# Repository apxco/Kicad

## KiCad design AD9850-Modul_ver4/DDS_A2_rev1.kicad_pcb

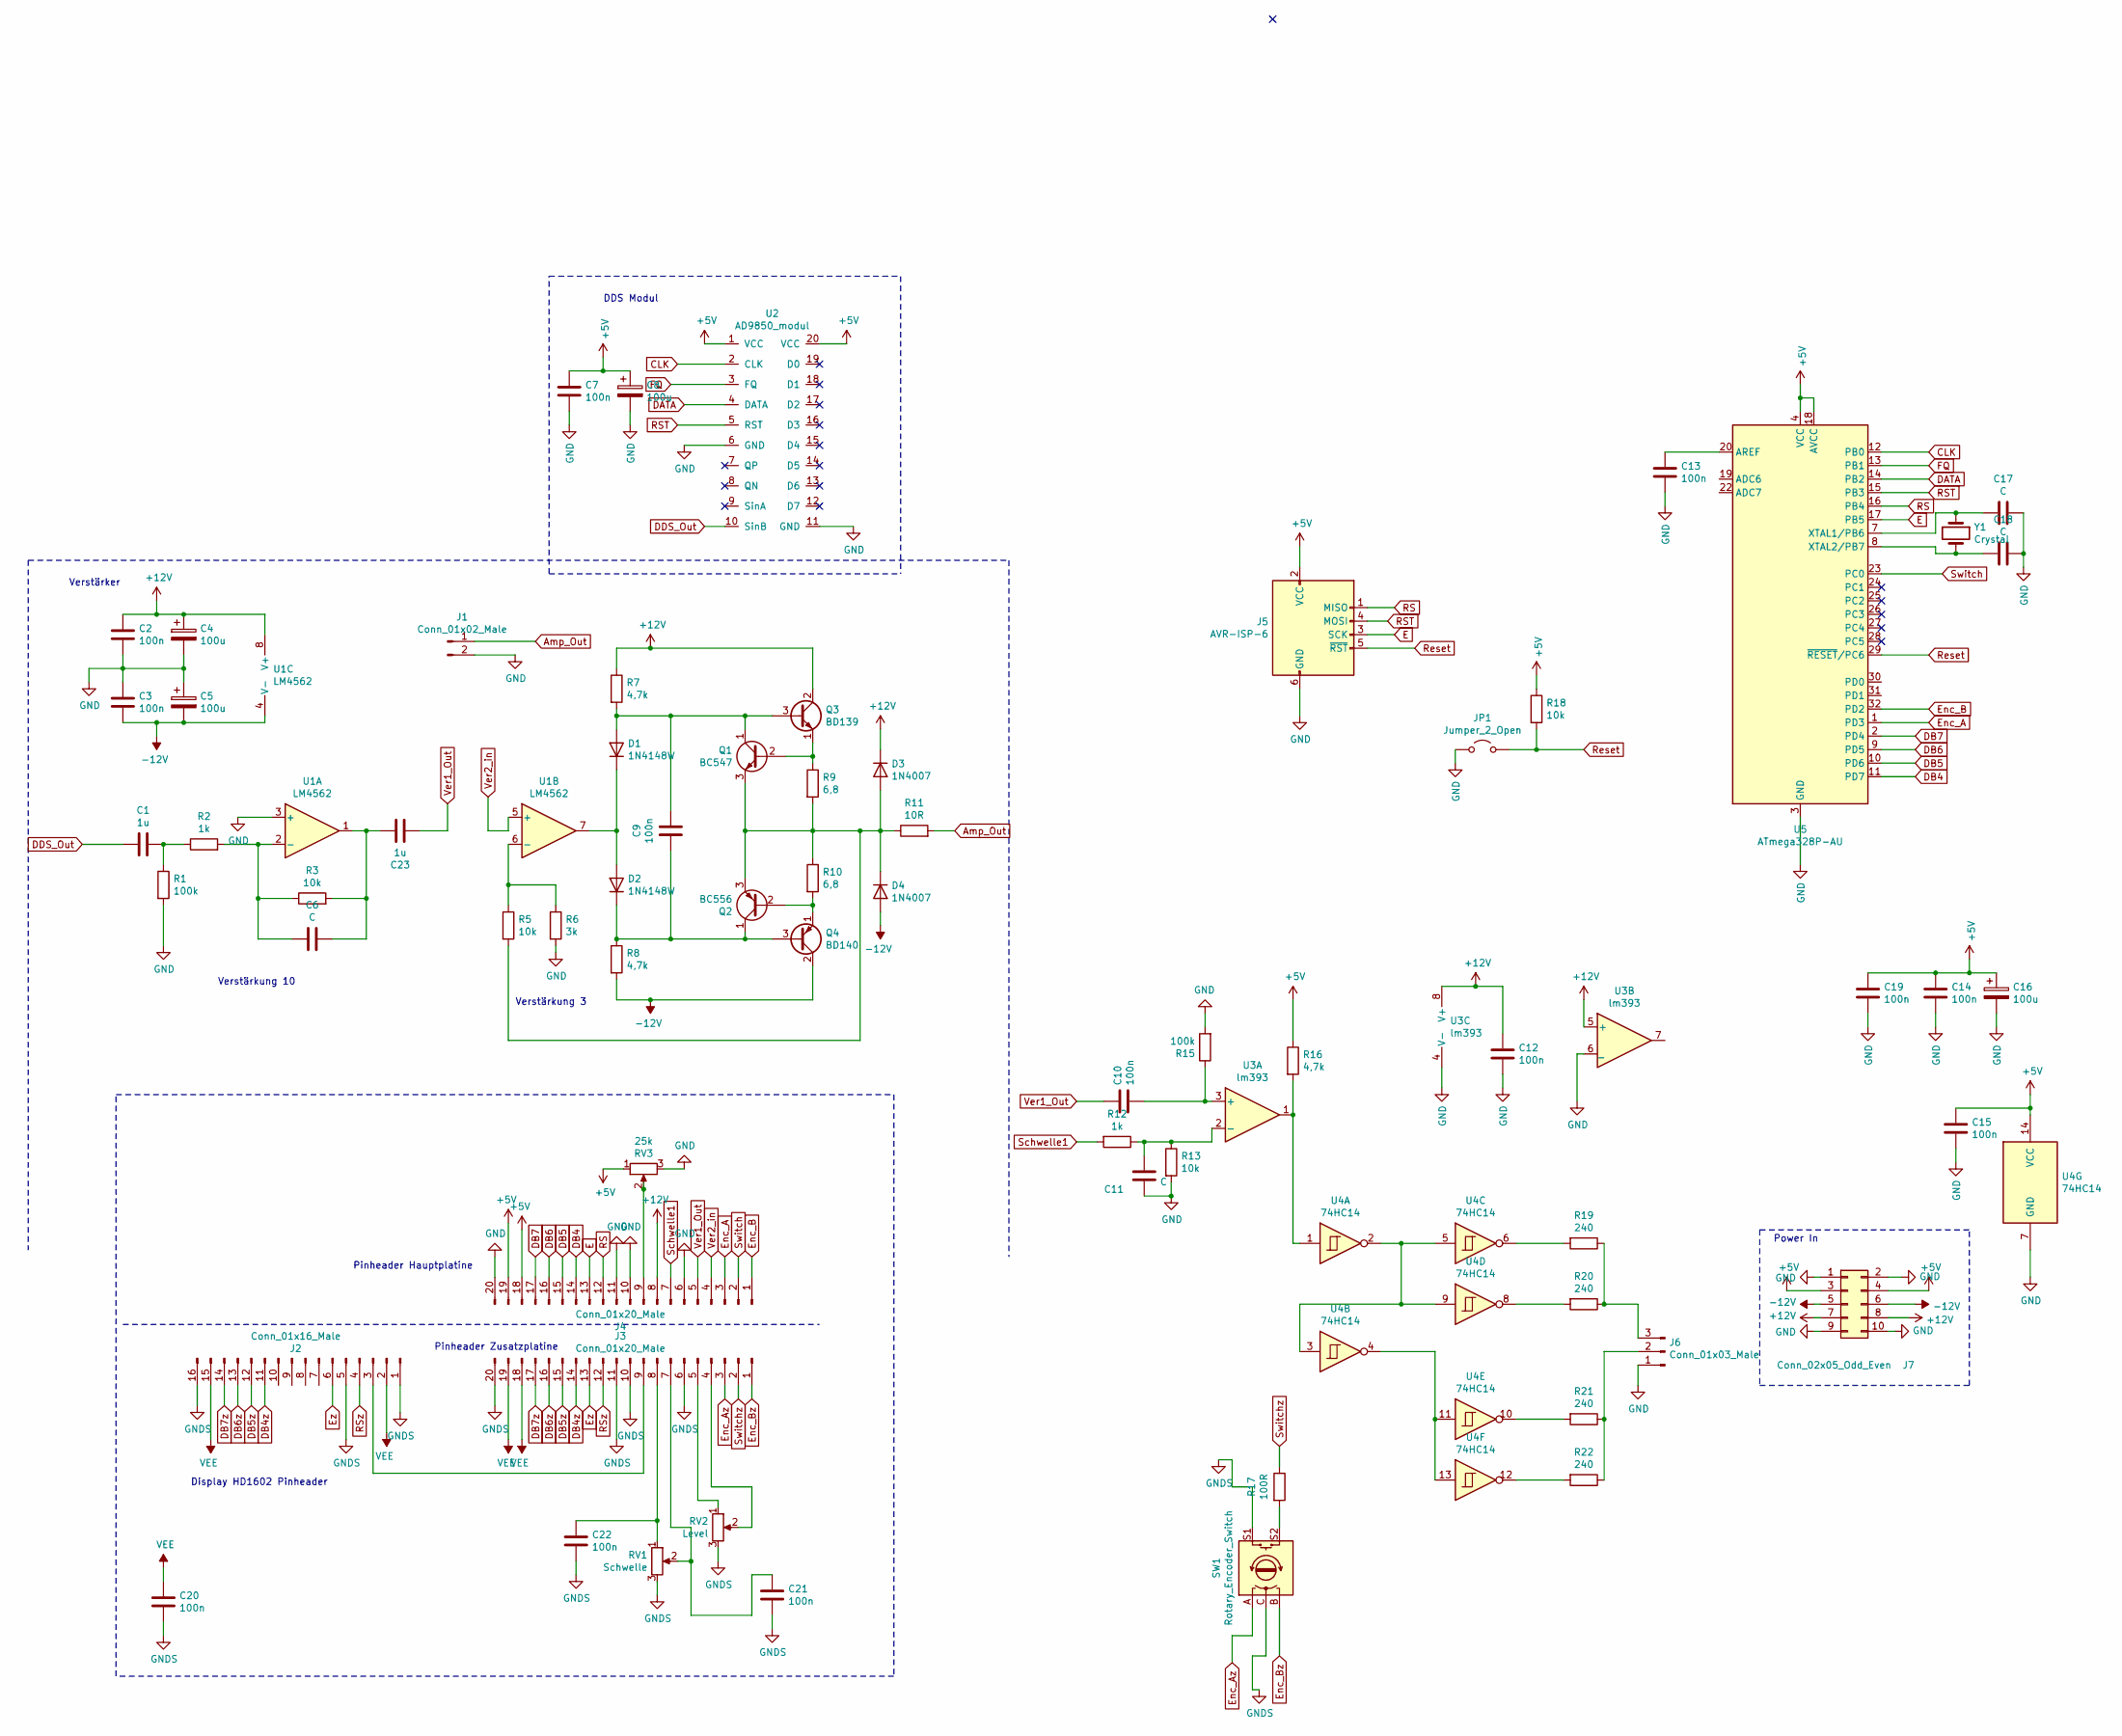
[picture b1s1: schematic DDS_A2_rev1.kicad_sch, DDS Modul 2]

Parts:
C1, C23: 1u; C_0805_2012Metric_Pad1.15x1.40mm_HandSolder
C2, C3, C7, C9, C10, C12, C13, C14, C15, C19, C20, C21, C22: 100n; C_0805_2012Metric_Pad1.15x1.40mm_HandSolder
C4, C5, C8, C16: 100u; CP_Radial_D5.0mm_P2.50mm
C6, C11: C; C_0805_2012Metric_Pad1.15x1.40mm_HandSolder
C17, C18: C; C_0603_1608Metric_Pad1.05x0.95mm_HandSolder
D1, D2: 1N4148W; D_SOD-123
D3, D4: 1N4007; D_DO-41_SOD81_P10.16mm_Horizontal
J1: Conn_01x02_Male; PinHeader_1x02_P2.54mm_Vertical
J2: Conn_01x16_Male; PinHeader_1x16_P2.54mm_Vertical
J3, J4: Conn_01x20_Male; PinHeader_1x20_P2.54mm_Vertical
J5: AVR-ISP-6; PinHeader_2x03_P2.54mm_Vertical
J6: Conn_01x03_Male; PinHeader_1x03_P2.54mm_Vertical
J7: Conn_02x05_Odd_Even; PinHeader_2x05_P2.54mm_Vertical
JP1: Jumper_2_Open; SolderJumper-2_P1.3mm_Bridged_Pad1.0x1.5mm
Q1: BC547; TO-92_Inline
Q2: BC556; TO-92_Inline
Q3: BD139; TO-126-3_Vertical
Q4: BD140; TO-126-3_Vertical
R1, R15: 100k; R_0805_2012Metric_Pad1.15x1.40mm_HandSolder
R2, R12: 1k; R_0805_2012Metric_Pad1.15x1.40mm_HandSolder
R3, R5, R13, R18: 10k; R_0805_2012Metric_Pad1.15x1.40mm_HandSolder
R6: 3k; R_0805_2012Metric_Pad1.15x1.40mm_HandSolder
R7, R8, R16: 4,7k; R_0805_2012Metric_Pad1.15x1.40mm_HandSolder
R9, R10: 6,8; R_2512_6332Metric_Pad1.52x3.35mm_HandSolder
R11: 10R; R_2512_6332Metric_Pad1.52x3.35mm_HandSolder
R17: 100R; R_0805_2012Metric_Pad1.15x1.40mm_HandSolder
R19, R20, R21, R22: 240; R_0805_2012Metric_Pad1.15x1.40mm_HandSolder
RV1: Schwelle; Potentiometer_Bourns_PTV09A-1_Single_Vertical
RV2: Level; Potentiometer_Bourns_PTV09A-1_Single_Vertical
RV3: 25k; Potentiometer_Bourns_3296W_Vertical
SW1: Rotary_Encoder_Switch; RotaryEncoder_Alps_EC11E-Switch_Vertical_H20mm
U1: LM4562; SOIC-8_3.9x4.9mm_P1.27mm
U2: AD9850_modul; AD9850modul
U3: lm393; SOIC-8_3.9x4.9mm_P1.27mm
U4: 74HC14; SOIC-14_3.9x8.7mm_P1.27mm
U5: ATmega328P-AU; TQFP-32_7x7mm_P0.8mm
Y1: Crystal; Crystal_HC18-U_Vertical

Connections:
+5V: C7.1, C8.1, C14.1, C15.1, C16.1, C19.1, J4.18, J4.19, J5.2 (VCC), J7.3, J7.4, R16.1, R18.1, RV3.1, U2.1 (VCC), U2.20 (VCC), U4.14 (VCC), U5.4 (VCC), U5.6 (VCC), U5.18 (AVCC)
+12V: C2.1, C4.1, C12.1, D3.1 (K), J4.8, J7.7, J7.8, Q3.2 (C), R7.1, U1.8 (V+), U3.5 (+), U3.8 (V+)
-12V: C3.2, C5.2, D4.2 (A), J7.5, J7.6, Q4.2 (C), R8.2, U1.4 (V-)
Amp_Out: J1.1, R11.2
CLK: U2.2 (CLK), U5.12 (PB0)
DATA: U2.4 (DATA), U5.14 (PB2)
DB4: J4.14, U5.11 (PD7)
DB4z: J2.11, J3.14
DB5: J4.15, U5.10 (PD6)
DB5z: J2.12, J3.15
DB6: J4.16, U5.9 (PD5)
DB6z: J2.13, J3.16
DB7: J4.17, U5.2 (PD4)
DB7z: J2.14, J3.17
DDS_Out: C1.2, U2.10 (SinB)
E: J4.13, J5.3 (SCK), U5.17 (PB5)
Enc_A: J4.3, U5.1 (PD3)
Enc_Az: J3.3, SW1.A
Enc_B: J4.1, U5.32 (PD2)
Enc_Bz: J3.1, SW1.B
Ez: J2.6, J3.13
FQ: U2.3 (FQ), U5.13 (PB1)
GND: C2.2, C3.1, C4.2, C5.1, C7.2, C8.2, C11.2, C12.2, C13.2, C14.2, C15.2, C16.2, C17.1, C18.1, C19.2, J1.2, J4.6, J4.10, J4.11, J4.20, J5.6 (GND), J6.1, J7.1, J7.2, J7.9, J7.10, JP1.1 (A), R1.2, R6.2, R13.2, R15.2, RV3.3, U1.3 (+), U2.6 (GND), U2.11 (GND), U3.4 (V-), U3.6 (_), U4.7 (GND), U5.3 (GND), U5.5 (GND), U5.21 (GND)
GNDS: C20.2, C21.2, C22.2, J2.1, J2.5, J2.16, J3.6, J3.10, J3.11, J3.20, RV1.3, RV2.3, SW1.C, SW1.S1
unnamed: C1.1, R1.1, R2.1
unnamed: C6.2, R2.2, R3.1, U1.2 (-)
unnamed: C9.1, D1.2 (A), Q1.1 (C), Q3.3 (B), R7.2
unnamed: C9.2, D2.1 (K), Q2.1 (C), Q4.3 (B), R8.1
unnamed: C10.2, R15.1, U3.3 (+)
unnamed: C11.1, R12.1, R13.1, U3.2 (-)
unnamed: C13.1, U5.20 (AREF)
unnamed: C17.2, U5.7 (XTAL1/PB6), Y1.1
unnamed: C18.2, U5.8 (XTAL2/PB7), Y1.2
unnamed: C21.1, J3.7, RV1.2
unnamed: C22.1, J3.8, RV1.1
unnamed: C6.1, C23.1, R3.2, U1.1
unnamed: D1.1 (K), D2.2 (A), U1.7
unnamed: D3.2 (A), D4.1 (K), Q1.3 (E), Q2.3 (E), R5.2, R9.2, R10.1, R11.1
unnamed: J2.3, J3.9
unnamed: J3.4, RV2.2
unnamed: J3.5, RV2.1
unnamed: J4.9, RV3.2
unnamed: J6.2, R21.1, R22.1
unnamed: J6.3, R19.1, R20.1
unnamed: Q1.2 (B), Q3.1 (E), R9.1
unnamed: Q2.2 (B), Q4.1 (E), R10.2
unnamed: R5.1, R6.1, U1.6 (-)
unnamed: R16.2, U3.1, U4.1
unnamed: R17.2, SW1.S2
unnamed: R19.2, U4.6
unnamed: R20.2, U4.8
unnamed: R21.2, U4.10
unnamed: R22.2, U4.12
unnamed: U4.2, U4.3, U4.5, U4.9
unnamed: U4.4, U4.11, U4.13
RS: J4.12, J5.1 (MISO), U5.16 (PB4)
RST: J5.4 (MOSI), U2.5 (RST), U5.15 (PB3)
RSz: J2.4, J3.12
Reset: J5.5 (~RST), JP1.2 (B), R18.2, U5.29 (~RESET/PC6)
Schwelle1: J4.7, R12.2
Switch: J4.2, U5.23 (PC0)
Switchz: J3.2, R17.1
VEE: C20.1, J2.2, J2.15, J3.18, J3.19
Ver1_Out: C10.1, C23.2, J4.5
Ver2_in: J4.4, U1.5 (+)

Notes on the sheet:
Pinheader Zusatzplatine
Verstärkung 3
Verstärker
Pinheader Hauptplatine
DDS Modul
Verstärkung 10
Power In
Display HD1602 Pinheader

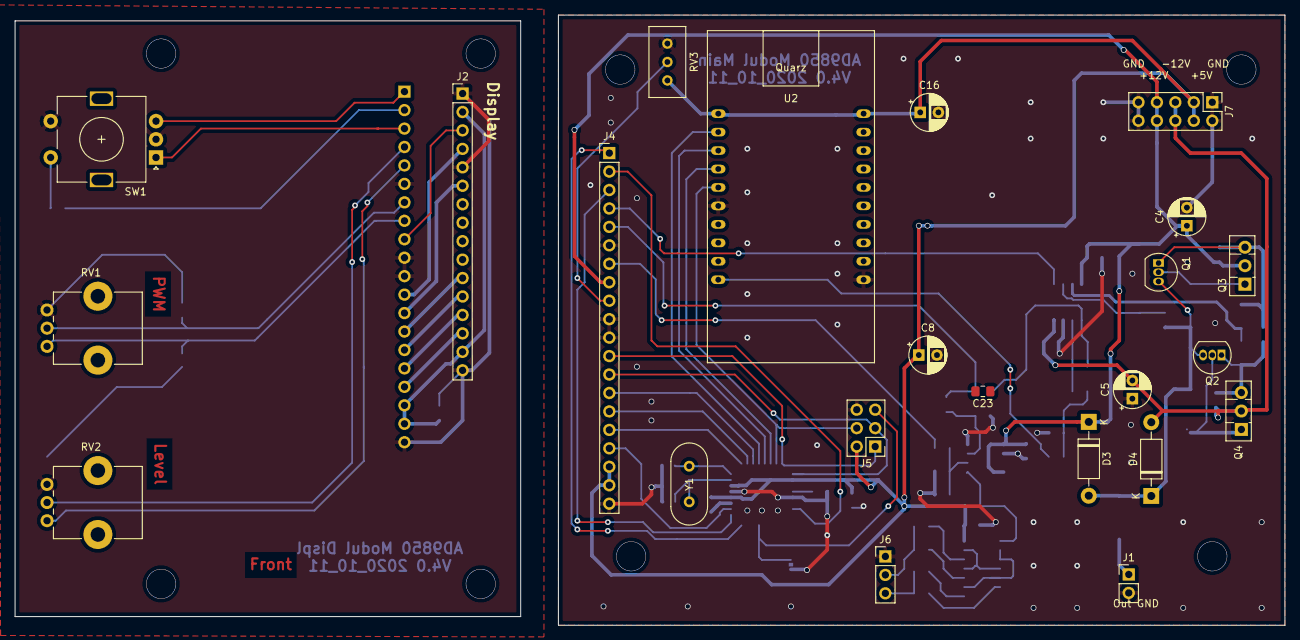
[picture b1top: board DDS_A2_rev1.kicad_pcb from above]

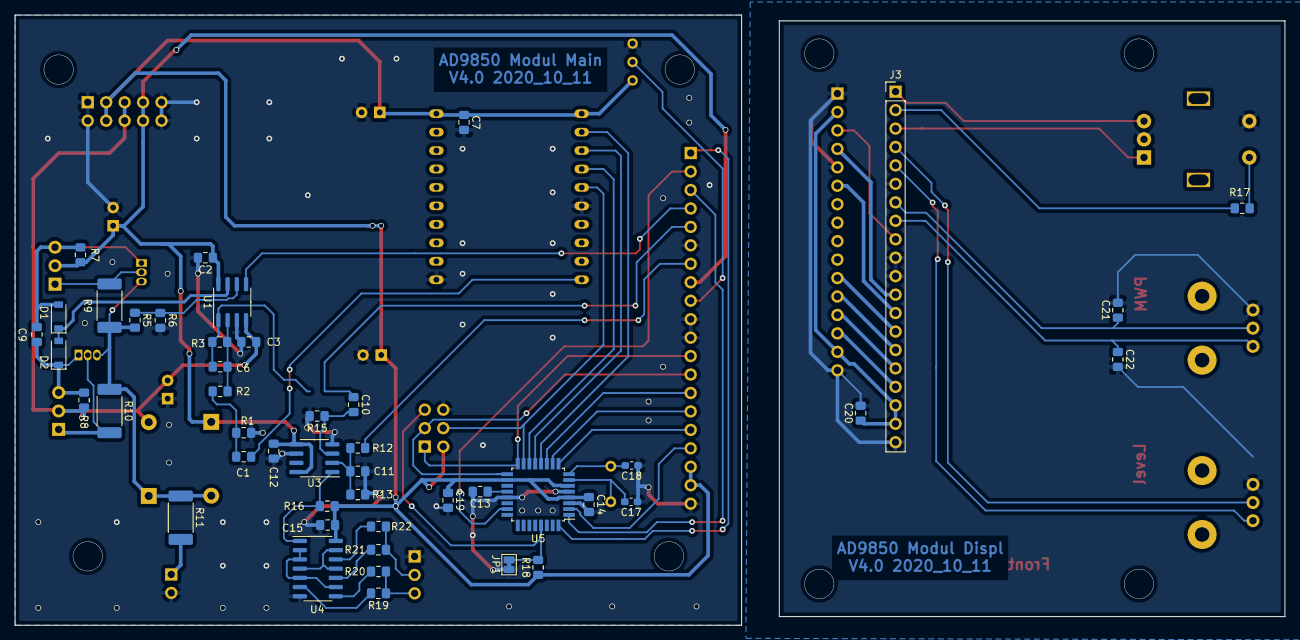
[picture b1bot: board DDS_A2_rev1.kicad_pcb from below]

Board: 2 copper layers, 100.0 x 84.0 mm, 69 parts (46 on the bottom side), 65 nets.

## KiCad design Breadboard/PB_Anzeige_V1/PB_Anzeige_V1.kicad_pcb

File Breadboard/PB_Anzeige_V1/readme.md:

Kleiner Helfer für Breadbords LED, Buzzer, Schalter, Poti

Aufgebaut funktioniert

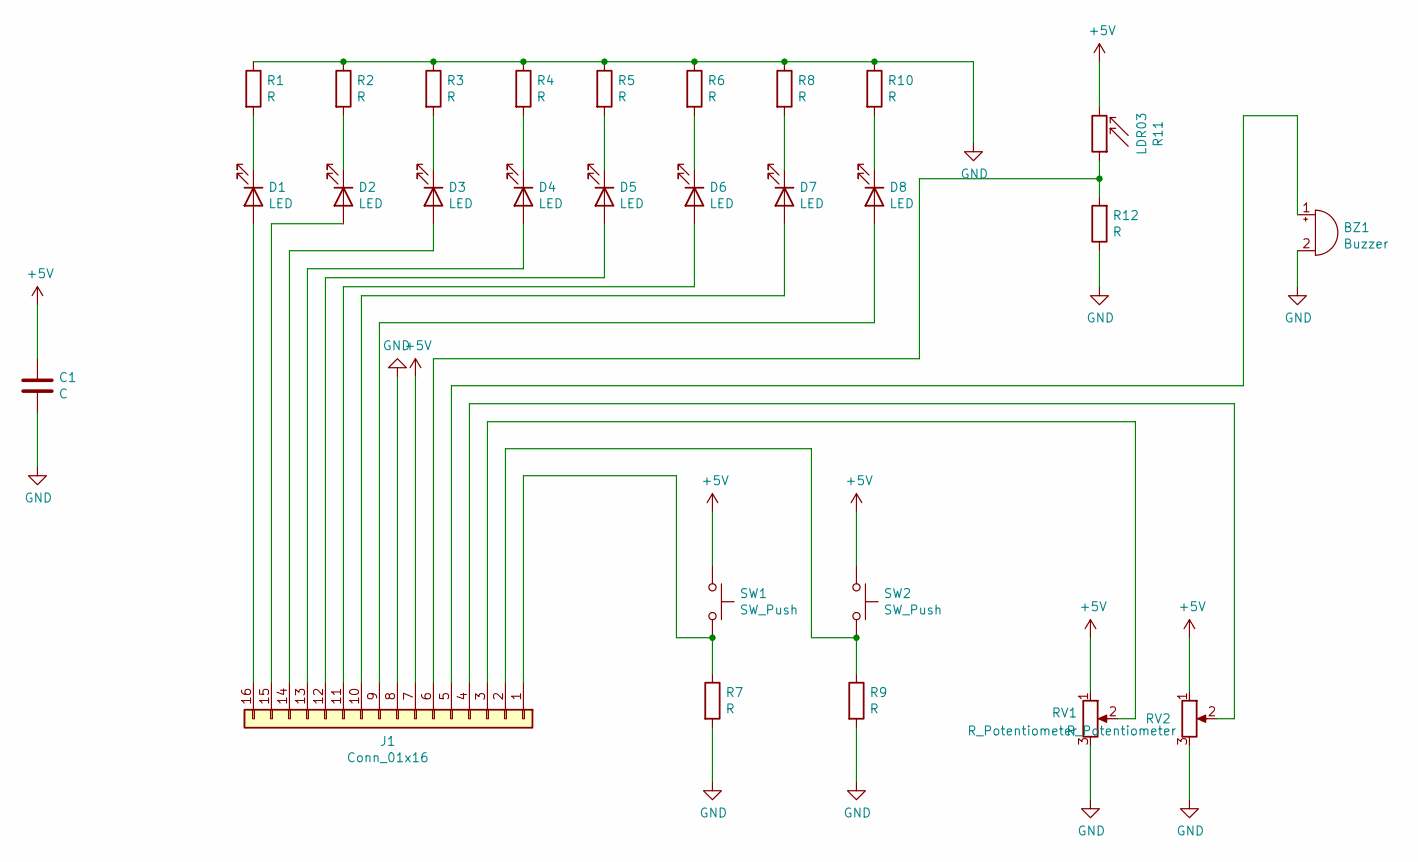
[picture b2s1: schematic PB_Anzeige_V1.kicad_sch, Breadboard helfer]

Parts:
BZ1: Buzzer; Buzzer_12x9.5RM7.6
C1: C; C_1206_3216Metric_Pad1.33x1.80mm_HandSolder
D1, D2, D3, D4, D5, D6, D7, D8: LED; LED_D3.0mm_Clear
J1: Conn_01x16; PinHeader_1x16_P2.54mm_Vertical
R1, R2, R3, R4, R5, R6, R7, R8, R9, R10, R12: R; R_0805_2012Metric_Pad1.20x1.40mm_HandSolder
R11: LDR03; R_LDR_10x8.5mm_P7.6mm_Vertical
RV1, RV2: R_Potentiometer; Potentiometer_Alps_RK09K_Single_Vertical
SW1, SW2: SW_Push; SW_PUSH_6mm_H4.3mm

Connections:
+5V: C1.1, J1.7, R11.2, RV1.1, RV2.1, SW1.1, SW2.1
GND: BZ1.2 (+), C1.2, J1.8, R1.1, R2.1, R3.1, R4.1, R5.1, R6.1, R7.2, R8.1, R9.2, R10.1, R12.1, RV1.3, RV2.3
unnamed: BZ1.1 (-), J1.5
unnamed: D1.1 (K), R1.2
unnamed: D1.2 (A), J1.16
unnamed: D2.1 (K), R2.2
unnamed: D2.2 (A), J1.15
unnamed: D3.1 (K), R3.2
unnamed: D3.2 (A), J1.14
unnamed: D4.1 (K), R4.2
unnamed: D4.2 (A), J1.13
unnamed: D5.1 (K), R5.2
unnamed: D5.2 (A), J1.12
unnamed: D6.1 (K), R6.2
unnamed: D6.2 (A), J1.11
unnamed: D7.1 (K), R8.2
unnamed: D7.2 (A), J1.10
unnamed: D8.1 (K), R10.2
unnamed: D8.2 (A), J1.9
unnamed: J1.1, R7.1, SW1.2
unnamed: J1.2, R9.1, SW2.2
unnamed: J1.3, RV1.2
unnamed: J1.4, RV2.2
unnamed: J1.6, R11.1, R12.2

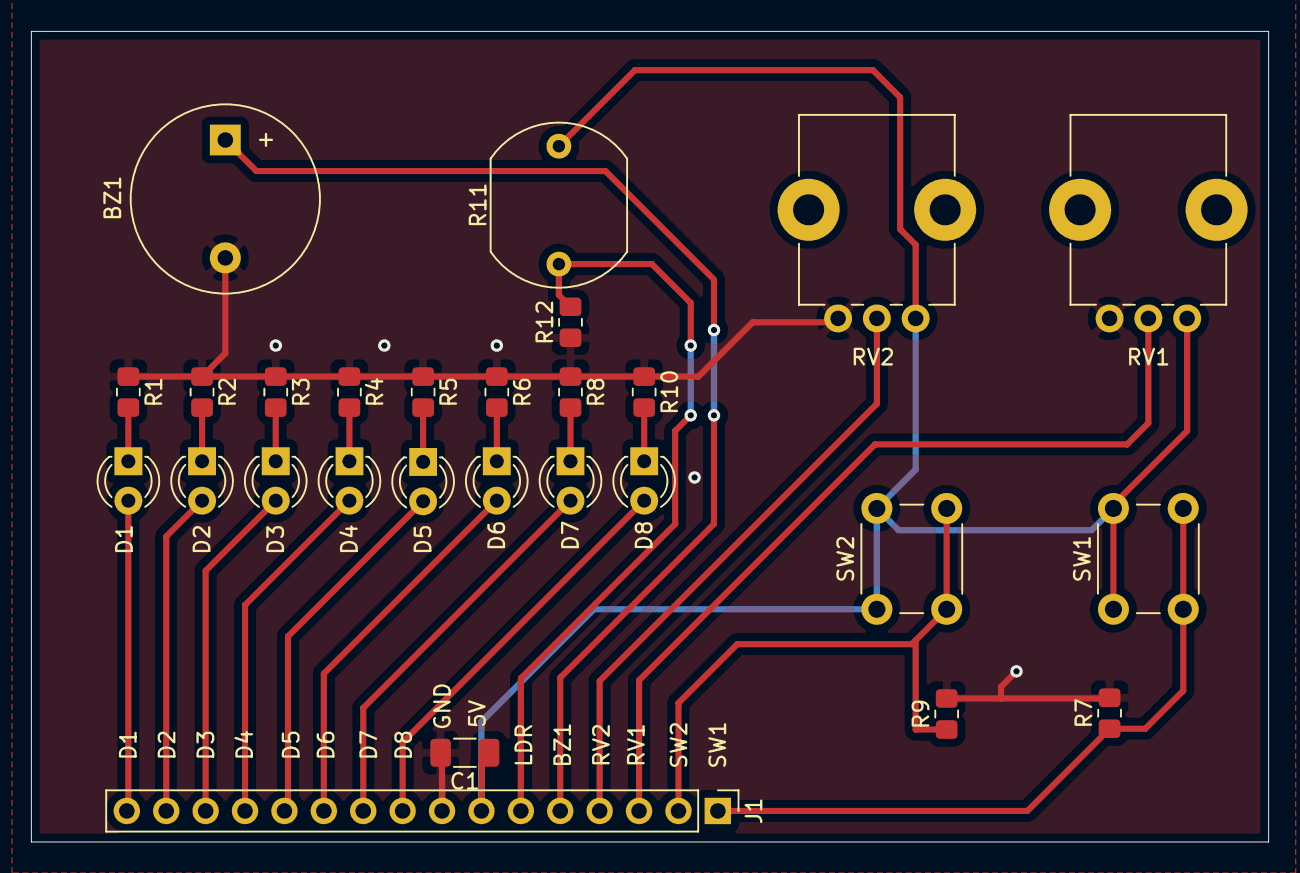
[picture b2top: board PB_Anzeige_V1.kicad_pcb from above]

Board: 2 copper layers, 79.8 x 52.2 mm, 27 parts (0 on the bottom side), 24 nets.

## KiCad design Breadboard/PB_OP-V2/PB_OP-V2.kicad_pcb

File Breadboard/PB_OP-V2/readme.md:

Doppel OP Zusatzboard für Breadboard, zum aufstecken auf die Kante für Spannungsversorgung

nicht fertig!

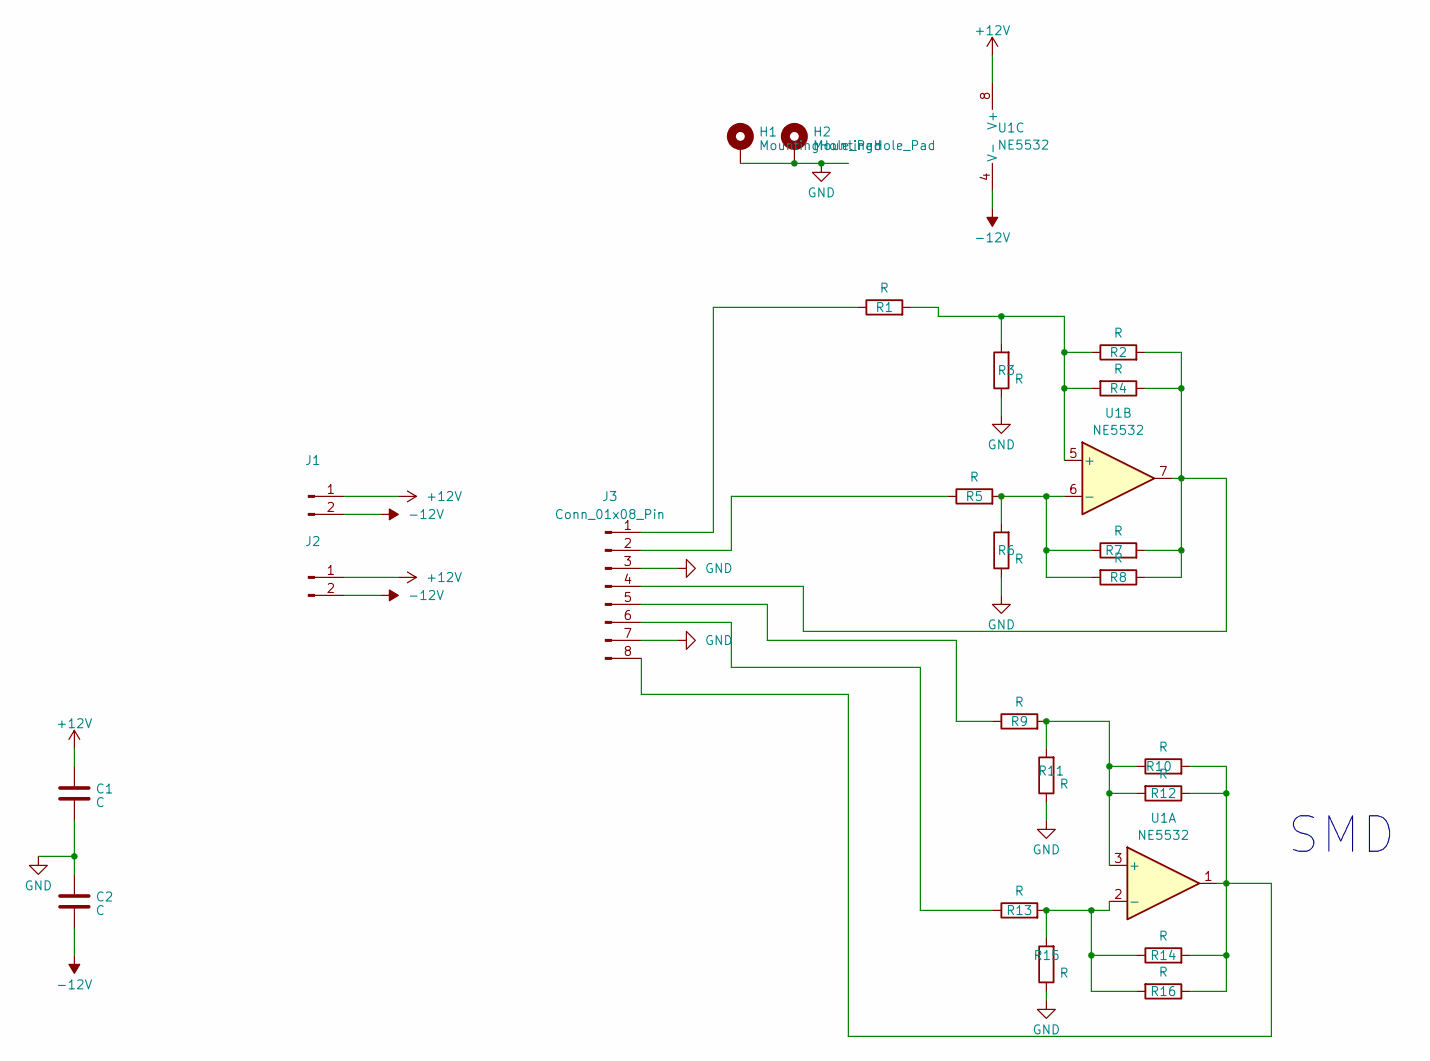
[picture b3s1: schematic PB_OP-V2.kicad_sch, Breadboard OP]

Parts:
C1, C2: C; C_0805_2012Metric_Pad1.18x1.45mm_HandSolder
H1, H2: MountingHole_Pad; MountingHole_3.2mm_M3_DIN965_Pad_TopBottom
J1, J2: Conn_01x02_Pin; PinSocket_1x02_P2.54mm_Vertical
J3: Conn_01x08_Pin; PinSocket_1x08_P2.54mm_Vertical
R1, R2, R3, R4, R5, R6, R7, R8: R; R_Axial_DIN0204_L3.6mm_D1.6mm_P7.62mm_Horizontal
R9, R10, R11, R12, R13, R14, R15, R16: R; R_0805_2012Metric_Pad1.20x1.40mm_HandSolder
U1: NE5532; SOIC-8_3.9x4.9mm_P1.27mm

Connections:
+12V: C1.1, J1.1, J2.1, U1.8 (V+)
-12V: C2.2, J1.2, J2.2, U1.4 (V-)
GND: C1.2, C2.1, H1.1, H2.1, J3.3, J3.7, R3.1, R6.1, R11.1, R15.1
unnamed: J3.1, R1.1
unnamed: J3.2, R5.1
unnamed: J3.4, R2.2, R4.1, R7.2, R8.1, U1.7
unnamed: J3.5, R9.1
unnamed: J3.6, R13.1
unnamed: J3.8, R10.2, R12.1, R14.2, R16.1, U1.1
unnamed: R9.2, R10.1, R11.2, R12.2, U1.3 (+)
unnamed: R13.2, R14.1, R15.2, R16.2, U1.2 (-)
unnamed: R1.2, R2.1, R3.2, R4.2, U1.5 (+)
unnamed: R5.2, R6.2, R7.1, R8.2, U1.6 (-)

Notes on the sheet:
SMD

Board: 2 copper layers, 24 parts (0 on the bottom side), 13 nets, no tracks yet.

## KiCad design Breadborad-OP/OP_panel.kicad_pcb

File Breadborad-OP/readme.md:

Doppel OP Zusatzboard für Breadboard, noch mit falschem Anschlusspins

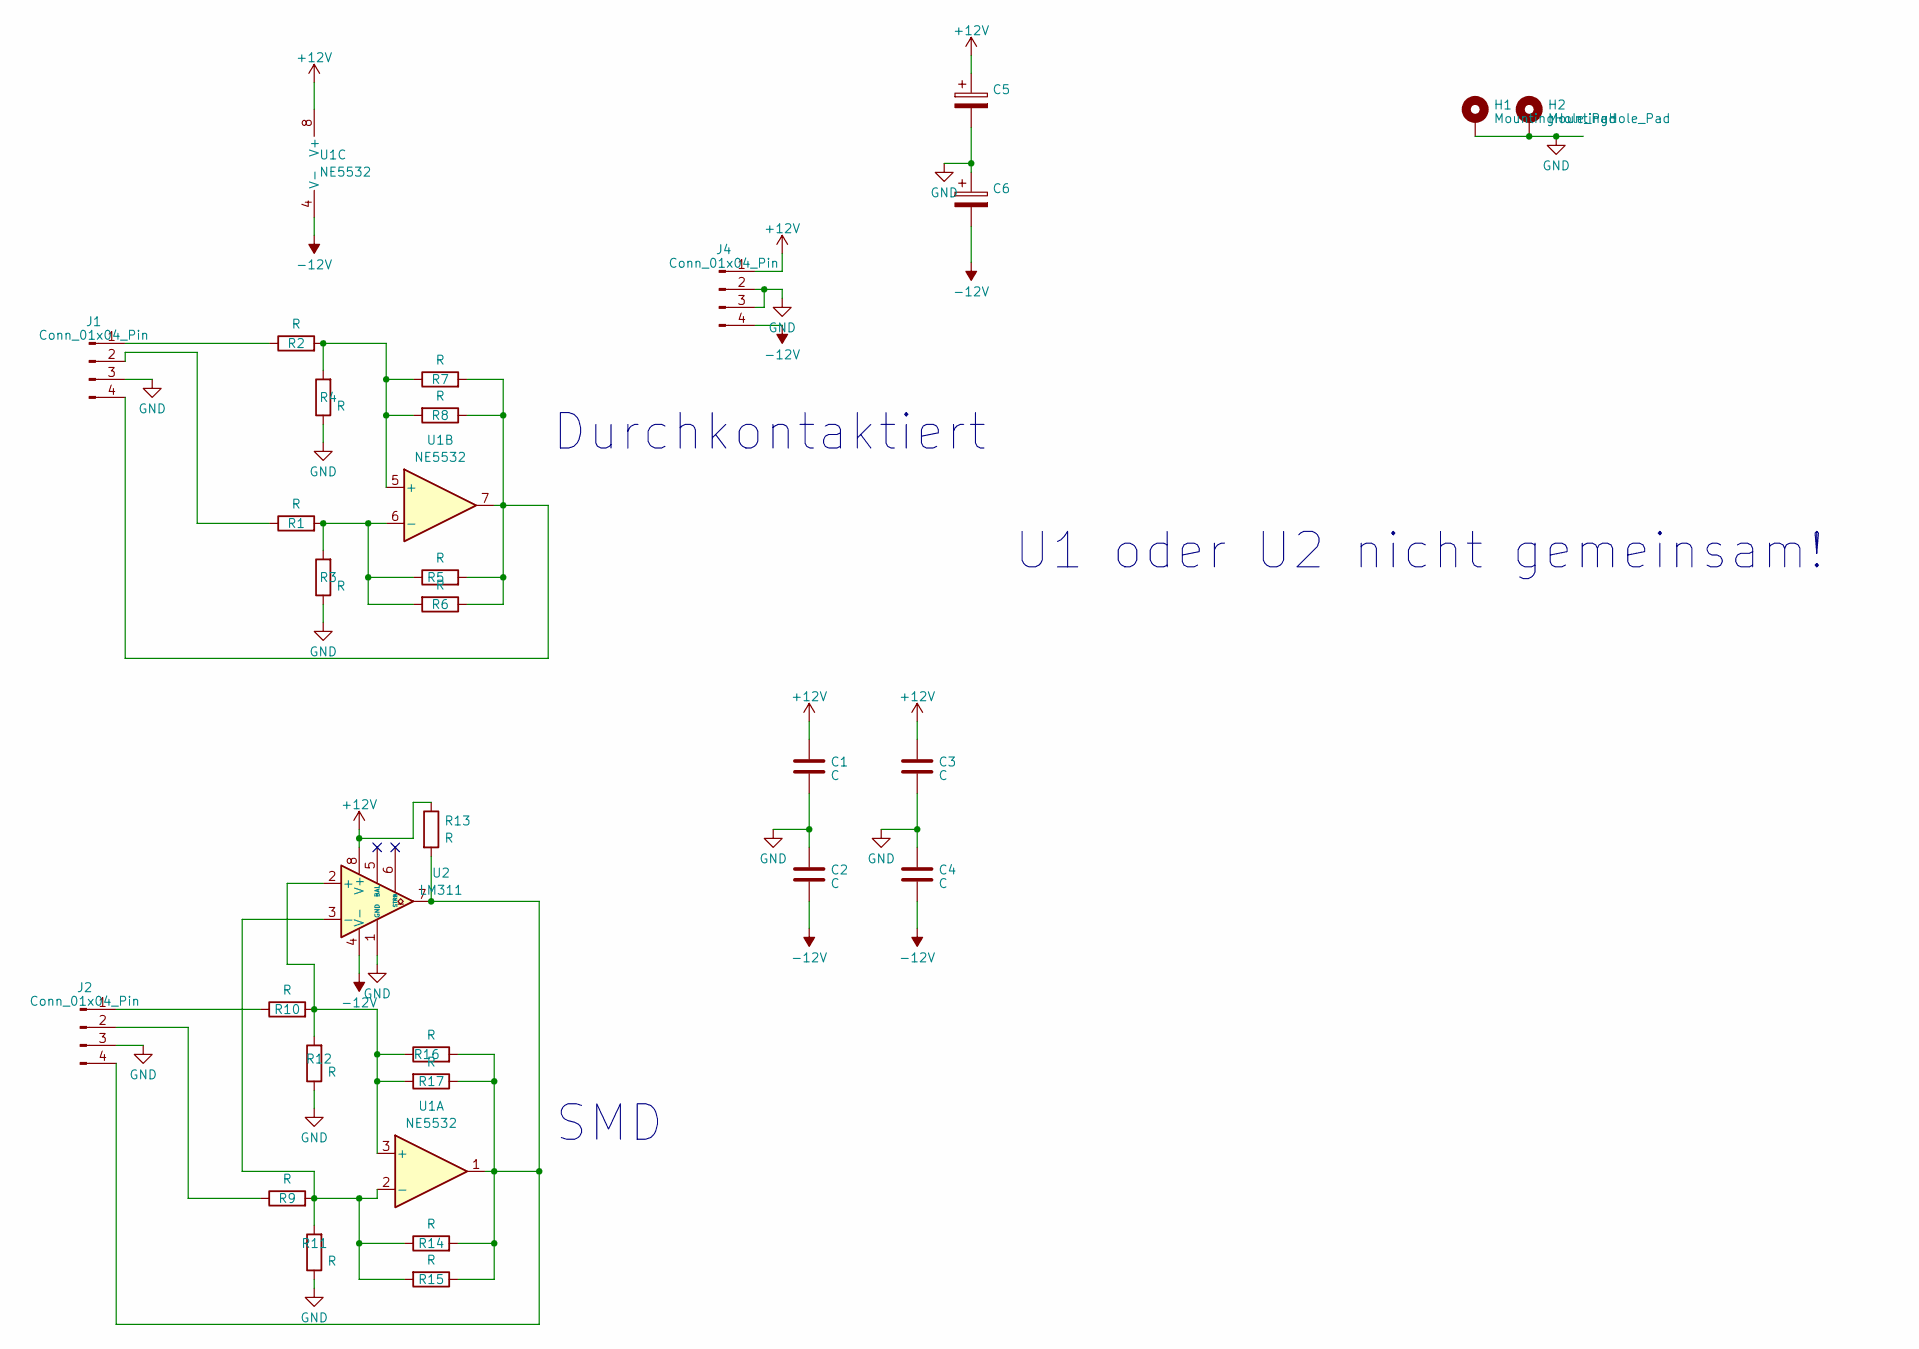
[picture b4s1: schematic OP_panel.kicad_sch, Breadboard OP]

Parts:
C1, C2, C3, C4: C; C_0805_2012Metric_Pad1.18x1.45mm_HandSolder
C5, C6: C_Polarized; CP_Elec_6.3x5.9
H1, H2: MountingHole_Pad; MountingHole_3.2mm_M3_DIN965_Pad_TopBottom
J1, J2: Conn_01x04_Pin; PinHeader_1x04_P2.54mm_Vertical
J4: Conn_01x04_Pin; PinSocket_1x04_P2.54mm_Vertical
R1, R2, R3, R4, R5, R6, R7, R8: R; R_Axial_DIN0204_L3.6mm_D1.6mm_P7.62mm_Horizontal
R9, R10, R11, R12, R13, R14, R15, R16, R17: R; R_0805_2012Metric_Pad1.20x1.40mm_HandSolder
U1: NE5532; SOIC-8_3.9x4.9mm_P1.27mm
U2: LM311; SOIC-8_3.9x4.9mm_P1.27mm

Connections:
+12V: C1.1, C3.1, C5.1, J4.1, R13.1, U1.8 (V+), U2.8 (V+)
-12V: C2.2, C4.2, C6.2, J4.4, U1.4 (V-), U2.4 (V-)
GND: C1.2, C2.1, C3.2, C4.1, C5.2, C6.1, H1.1, H2.1, J1.3, J2.3, J4.2, J4.3, R3.1, R4.1, R11.1, R12.1, U2.1 (GND)
unnamed: J1.1, R2.1
unnamed: J1.2, R1.1
unnamed: J1.4, R5.2, R6.1, R7.2, R8.1, U1.7
unnamed: J2.1, R10.1
unnamed: J2.2, R9.1
unnamed: J2.4, R13.2, R14.2, R15.1, R16.2, R17.1, U1.1, U2.7
unnamed: R10.2, R12.2, R16.1, R17.2, U1.3 (+), U2.2 (+)
unnamed: R9.2, R11.2, R14.1, R15.2, U1.2 (-), U2.3 (-)
unnamed: R2.2, R4.2, R7.1, R8.2, U1.5 (+)
unnamed: R1.2, R3.2, R5.1, R6.2, U1.6 (-)

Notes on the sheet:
U1 oder U2 nicht gemeinsam!
Durchkontaktiert
SMD

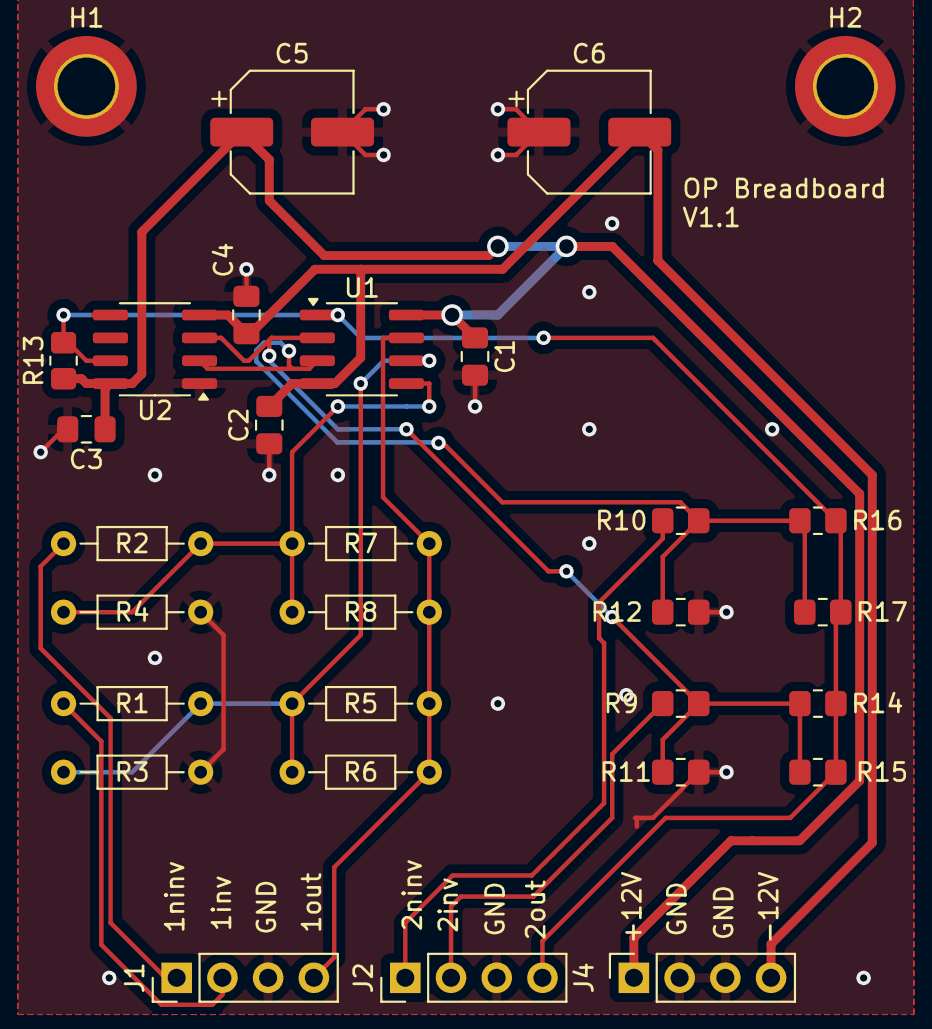
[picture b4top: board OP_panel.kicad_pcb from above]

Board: 2 copper layers, 30 parts (0 on the bottom side), 13 nets.

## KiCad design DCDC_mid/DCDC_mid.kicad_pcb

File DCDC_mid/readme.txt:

Richtig schlechter DC DC Step Down Wandler mit 12V Ausgangsspannung. Mehr als Machbarkietsstudie zu verstehen. In dieser Version funktioniert er, Spulenwert und Typen der Dioden nicht zu ernst nehmen.

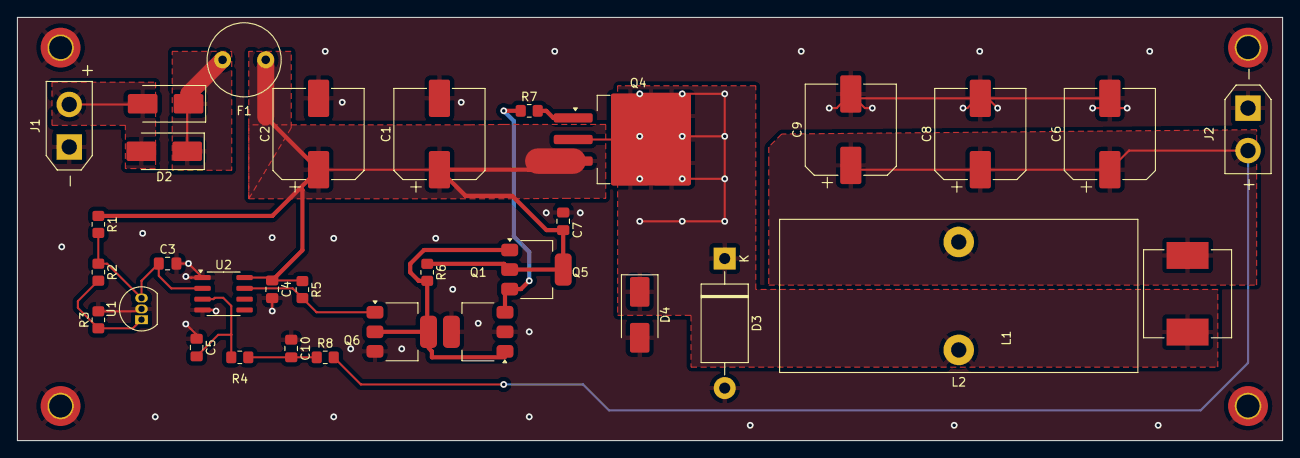
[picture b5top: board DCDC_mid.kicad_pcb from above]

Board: 2 copper layers, 148.8 x 49.8 mm, 37 parts (0 on the bottom side), 14 nets.

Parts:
C1, C2, C6, C8, C9: C_Polarized; CP_Elec_10x12.5
C3, C4, C5, C7, C10: 100n; C_0805_2012Metric_Pad1.18x1.45mm_HandSolder
D1, D2, D4: D; D_SMB_Handsoldering
D3: D; D_DO-201AE_P15.24mm_Horizontal
F1: Fuse; Fuse_Littelfuse_372_D8.50mm
H1, H2, H3, H4: MountingHole_Pad; MountingHole_2.7mm_M2.5_DIN965_Pad_TopOnly
J1, J2: Conn_01x02_Pin; AMASS_XT30UPB-M_1x02_P5.0mm_Vertical
L1: L; L_Vishay_IHLP-4040
L2: L; L_Toroid_Vertical_L41.9mm_W17.8mm_P12.70mm_Pulse_F
Q1: FTZ953; SOT-223-3_TabPin2
Q4: Q_PMOS_GDSD; TO-263-3_TabPin4
Q5, Q6: FTZ853; SOT-223-3_TabPin2
R1: 680; R_0805_2012Metric_Pad1.20x1.40mm_HandSolder
R2, R4, R8: 13k; R_0805_2012Metric_Pad1.20x1.40mm_HandSolder
R3, R5: 3k; R_0805_2012Metric_Pad1.20x1.40mm_HandSolder
R6: 100; R_0805_2012Metric_Pad1.20x1.40mm_HandSolder
R7: 1R; R_0805_2012Metric_Pad1.20x1.40mm_HandSolder
U1: TL431LP; TO-92_Inline
U2: LM311; SOIC-8_3.9x4.9mm_P1.27mm

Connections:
+VDC: C1.1, C2.1, C4.1, C7.2, F1.2, Q4.3 (S), Q5.2 (C), R1.1, R5.1, R6.1, U2.8 (V+)
GND: C1.2, C2.2, C3.2, C4.2, C5.1, C6.2, C7.1, C8.2, C9.2, C10.1, D3.2 (A), D4.2 (A), H1.1, H2.1, H3.1, H4.1, J1.1, J2.1, Q1.2 (C), Q6.3 (E), R3.2, U1.2 (A), U2.1 (GND), U2.4 (V-)
unnamed: C10.2, R4.2, R8.1
unnamed: D1.2 (A), D2.2 (A), J1.2
unnamed: D1.1 (K), D2.1 (K), F1.1
unnamed: D3.1 (K), D4.1 (K), L1.1, L2.1, Q4.2 (D), Q4.4 (D)
unnamed: C6.1, C8.1, C9.1, J2.2, L1.2, L2.2, R8.2
unnamed: Q1.1 (B), Q5.1 (B), Q6.2 (C), R6.2
unnamed: Q1.3 (E), Q5.3 (E), R7.1
unnamed: Q4.1 (G), R7.2
unnamed: Q6.1 (B), R5.2, U2.7
unnamed: C3.1, R1.2, R2.1, U1.3 (K), U2.2 (+)
unnamed: R2.2, R3.1, U1.1 (REF)
unnamed: C5.2, R4.1, U2.3 (-)

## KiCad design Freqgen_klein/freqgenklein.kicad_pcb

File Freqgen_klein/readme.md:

Kleiner Oszillator zu testzwecken

Aufgebaut funktioniert

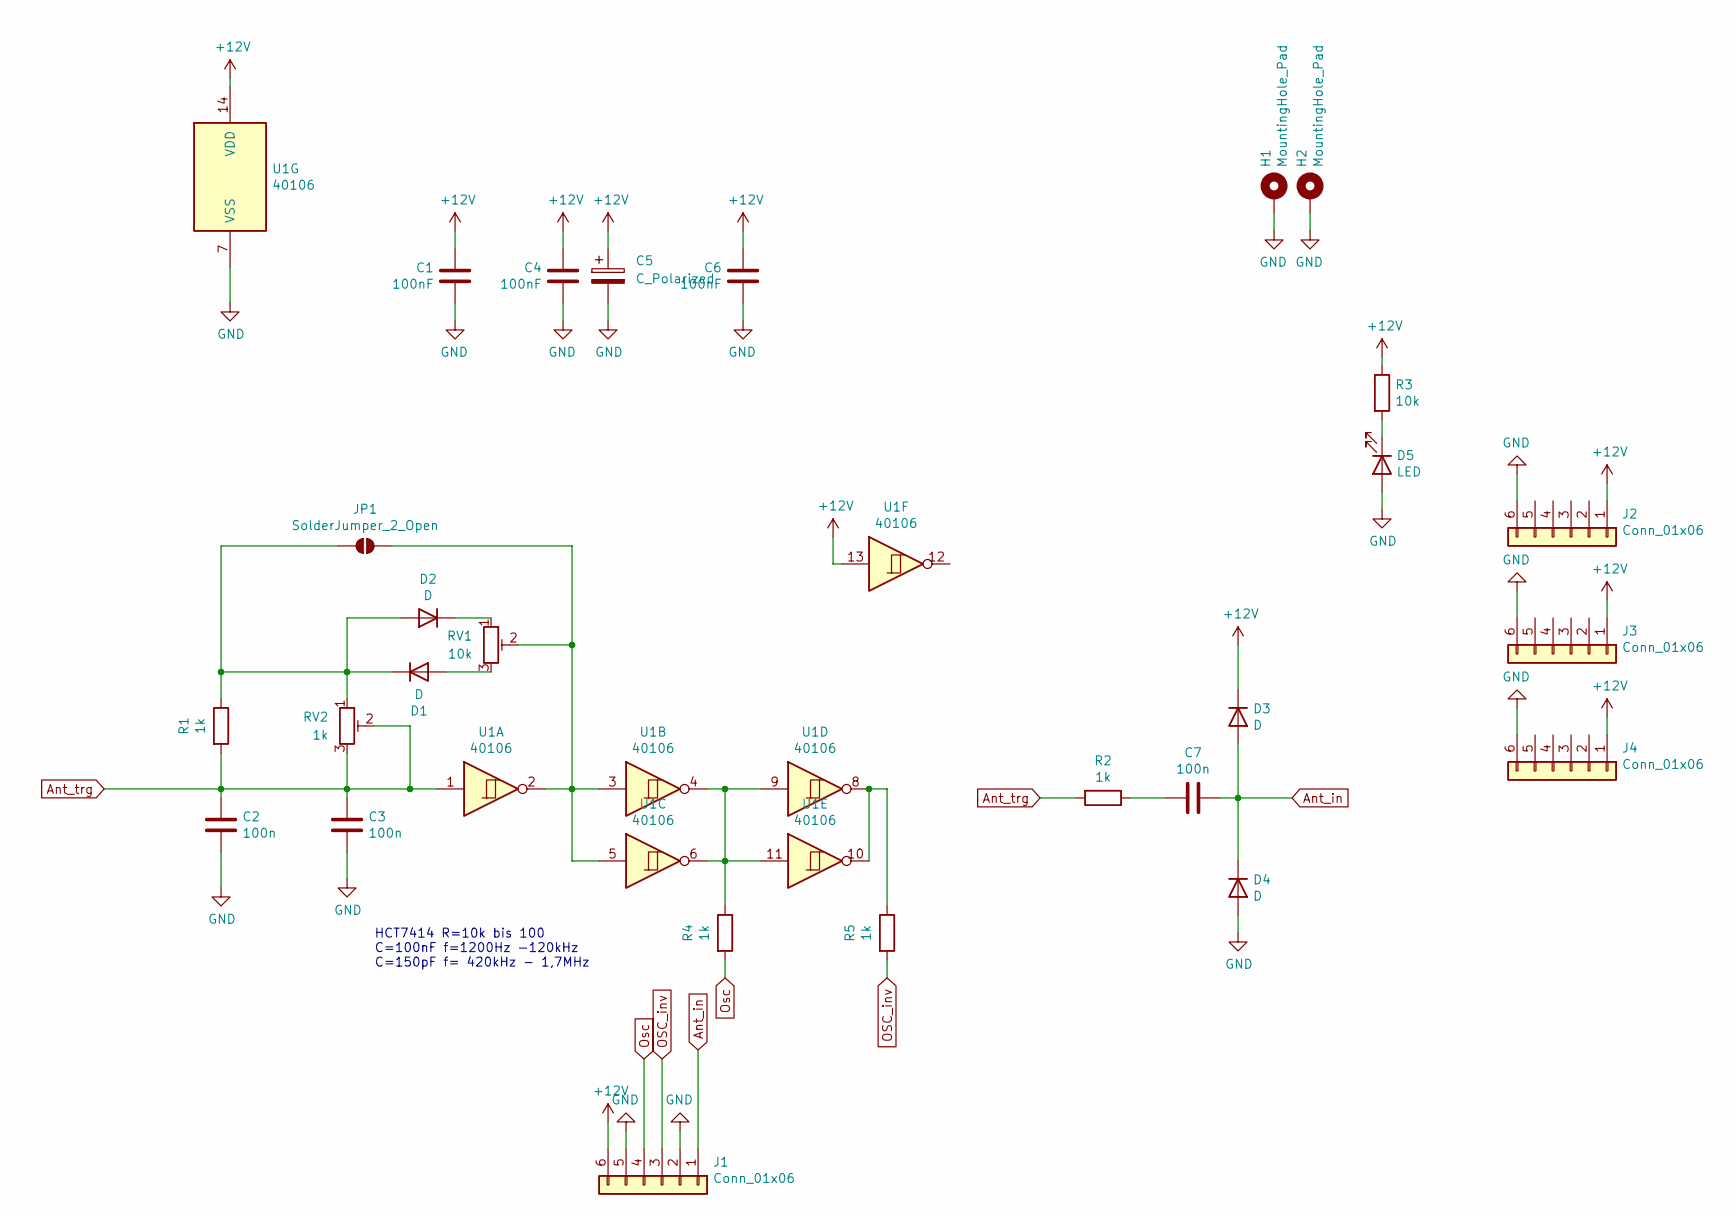
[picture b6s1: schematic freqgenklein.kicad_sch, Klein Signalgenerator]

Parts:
C1, C4, C6: 100nF; C_0805_2012Metric_Pad1.18x1.45mm_HandSolder
C2, C7: 100n; C_Axial_L3.8mm_D2.6mm_P7.50mm_Horizontal
C3: 100n; C_0805_2012Metric_Pad1.18x1.45mm_HandSolder
C5: C_Polarized; CP_Elec_10x10.5
D1, D2: D; D_0805_2012Metric_Pad1.15x1.40mm_HandSolder
D3, D4: D; C_0805_2012Metric_Pad1.18x1.45mm_HandSolder
D5: LED; LED_0805_2012Metric_Pad1.15x1.40mm_HandSolder
H1, H2: MountingHole_Pad; MountingHole_3.2mm_M3_DIN965_Pad
J1, J2, J3, J4: Conn_01x06; PinSocket_1x06_P2.54mm_Vertical
JP1: SolderJumper_2_Open; SolderJumper-2_P1.3mm_Open_TrianglePad1.0x1.5mm
R1, R2, R4, R5: 1k; R_0805_2012Metric_Pad1.20x1.40mm_HandSolder
R3: 10k; R_0805_2012Metric_Pad1.20x1.40mm_HandSolder
RV1: 10k; Potentiometer_Bourns_3296W_Vertical
RV2: 1k; Potentiometer_Bourns_3296W_Vertical
U1: 40106; SO-14_3.9x8.65mm_P1.27mm

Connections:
+12V: C1.1, C4.1, C5.1, C6.1, D3.1 (K), J1.6, J2.1, J3.1, J4.1, R3.1, U1.13, U1.14 (VDD)
Ant_in: C7.1, D3.2 (A), D4.1 (K), J1.1
Ant_trg: C2.1, C3.1, R1.2, R2.2, RV2.2, RV2.3, U1.1
GND: C1.2, C2.2, C3.2, C4.2, C5.2, C6.2, D4.2 (A), D5.2 (A), H1.1, H2.1, J1.2, J1.5, J2.6, J3.6, J4.6, U1.7 (VSS)
unnamed: C7.2, R2.1
unnamed: D1.2 (A), RV1.3
unnamed: D1.1 (K), D2.2 (A), JP1.1 (A), R1.1, RV2.1
unnamed: D2.1 (K), RV1.1
unnamed: D5.1 (K), R3.2
unnamed: JP1.2 (B), RV1.2, U1.2, U1.3, U1.5
unnamed: R4.1, U1.4, U1.6, U1.9, U1.11
unnamed: R5.1, U1.8, U1.10
OSC_inv: J1.3, R5.2
Osc: J1.4, R4.2

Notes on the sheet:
HCT7414 R=10k bis 100 C=100nF f=1200Hz -120kHz C=150pF f= 420kHz - 1,7MHz
